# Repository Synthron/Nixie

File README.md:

# Nixie

A Nixie Clock with Z5600M and ESP32

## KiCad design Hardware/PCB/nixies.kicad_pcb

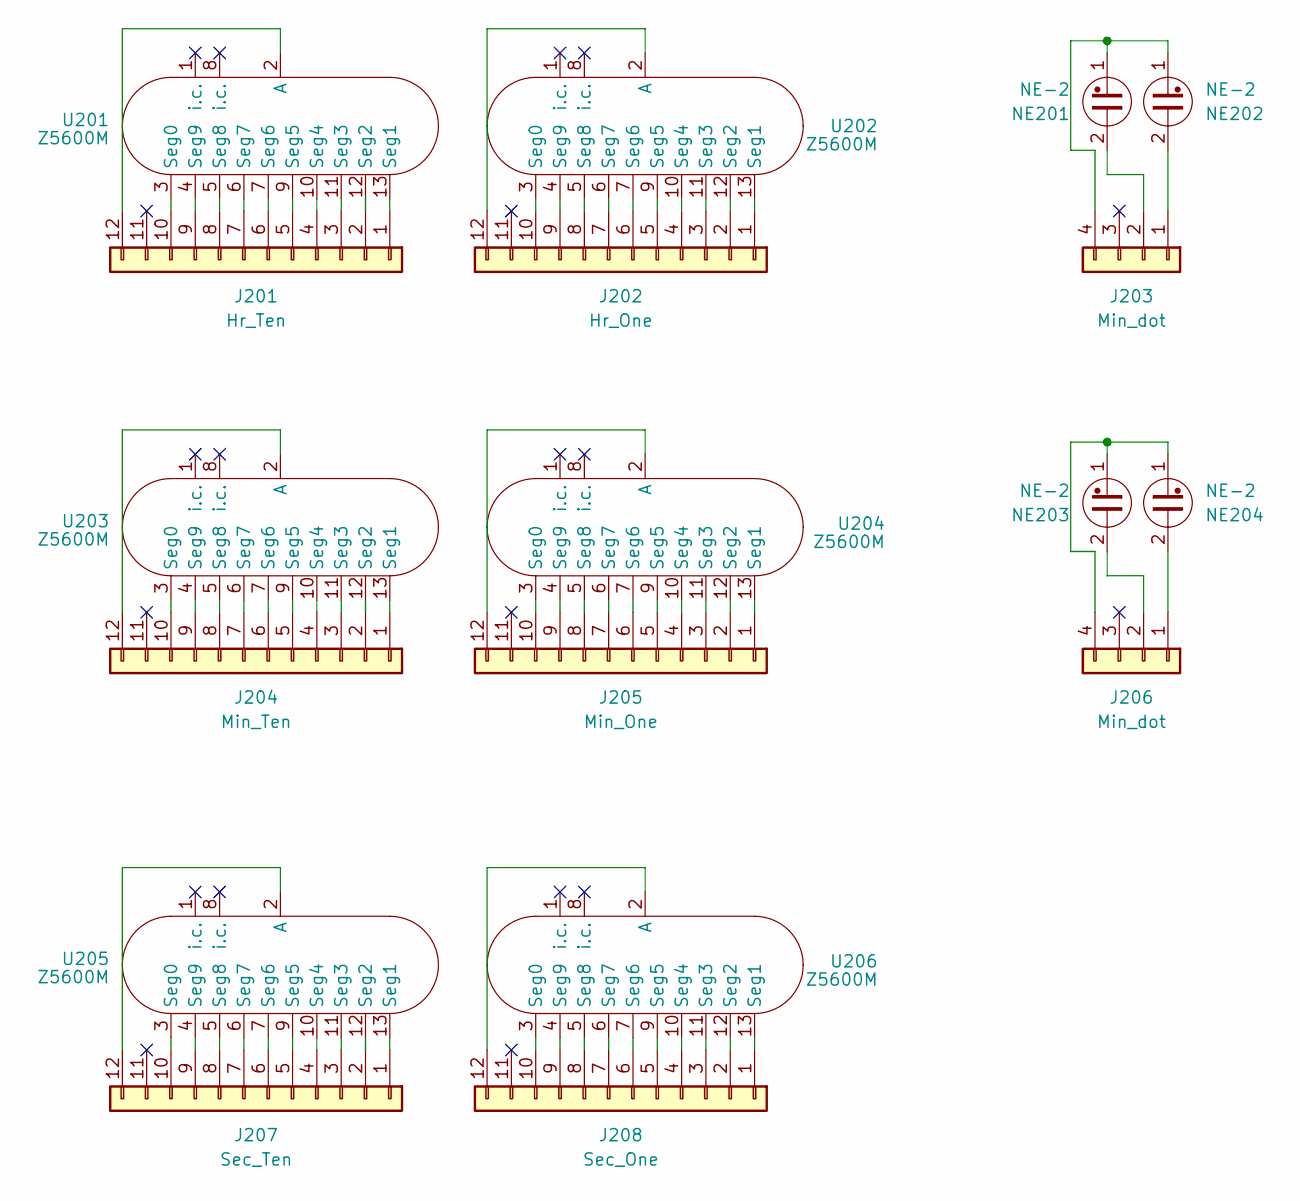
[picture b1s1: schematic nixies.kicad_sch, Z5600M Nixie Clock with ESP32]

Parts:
J201: Hr_Ten; PinSocket_1x12_P2.54mm_Vertical
J202: Hr_One; PinSocket_1x12_P2.54mm_Vertical
J203, J206: Min_dot; PinSocket_1x04_P2.54mm_Vertical
J204: Min_Ten; PinSocket_1x12_P2.54mm_Vertical
J205: Min_One; PinSocket_1x12_P2.54mm_Vertical
J207: Sec_Ten; PinSocket_1x12_P2.54mm_Vertical
J208: Sec_One; PinSocket_1x12_P2.54mm_Vertical
NE201, NE202, NE203, NE204: NE-2; Valve_Glimm
U201, U202, U203, U204, U205, U206: Z5600M; B13B

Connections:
unnamed: J201.1, U201.13 (Seg1)
unnamed: J201.2, U201.12 (Seg2)
unnamed: J201.3, U201.11 (Seg3)
unnamed: J201.4, U201.10 (Seg4)
unnamed: J201.5, U201.9 (Seg5)
unnamed: J201.6, U201.7 (Seg6)
unnamed: J201.7, U201.6 (Seg7)
unnamed: J201.8, U201.5 (Seg8)
unnamed: J201.9, U201.4 (Seg9)
unnamed: J201.10, U201.3 (Seg0)
unnamed: J201.12, U201.2 (A)
unnamed: J202.1, U202.13 (Seg1)
unnamed: J202.2, U202.12 (Seg2)
unnamed: J202.3, U202.11 (Seg3)
unnamed: J202.4, U202.10 (Seg4)
unnamed: J202.5, U202.9 (Seg5)
unnamed: J202.6, U202.7 (Seg6)
unnamed: J202.7, U202.6 (Seg7)
unnamed: J202.8, U202.5 (Seg8)
unnamed: J202.9, U202.4 (Seg9)
unnamed: J202.10, U202.3 (Seg0)
unnamed: J202.12, U202.2 (A)
unnamed: J203.1, NE202.2
unnamed: J203.2, NE201.2
unnamed: J203.4, NE201.1, NE202.1
unnamed: J204.1, U203.13 (Seg1)
unnamed: J204.2, U203.12 (Seg2)
unnamed: J204.3, U203.11 (Seg3)
unnamed: J204.4, U203.10 (Seg4)
unnamed: J204.5, U203.9 (Seg5)
unnamed: J204.6, U203.7 (Seg6)
unnamed: J204.7, U203.6 (Seg7)
unnamed: J204.8, U203.5 (Seg8)
unnamed: J204.9, U203.4 (Seg9)
unnamed: J204.10, U203.3 (Seg0)
unnamed: J204.12, U203.2 (A)
unnamed: J205.1, U204.13 (Seg1)
unnamed: J205.2, U204.12 (Seg2)
unnamed: J205.3, U204.11 (Seg3)
unnamed: J205.4, U204.10 (Seg4)
unnamed: J205.5, U204.9 (Seg5)
unnamed: J205.6, U204.7 (Seg6)
unnamed: J205.7, U204.6 (Seg7)
unnamed: J205.8, U204.5 (Seg8)
unnamed: J205.9, U204.4 (Seg9)
unnamed: J205.10, U204.3 (Seg0)
unnamed: J205.12, U204.2 (A)
unnamed: J206.1, NE204.2
unnamed: J206.2, NE203.2
unnamed: J206.4, NE203.1, NE204.1
unnamed: J207.1, U205.13 (Seg1)
unnamed: J207.2, U205.12 (Seg2)
unnamed: J207.3, U205.11 (Seg3)
unnamed: J207.4, U205.10 (Seg4)
unnamed: J207.5, U205.9 (Seg5)
unnamed: J207.6, U205.7 (Seg6)
unnamed: J207.7, U205.6 (Seg7)
unnamed: J207.8, U205.5 (Seg8)
unnamed: J207.9, U205.4 (Seg9)
unnamed: J207.10, U205.3 (Seg0)
unnamed: J207.12, U205.2 (A)
unnamed: J208.1, U206.13 (Seg1)
unnamed: J208.2, U206.12 (Seg2)
unnamed: J208.3, U206.11 (Seg3)
unnamed: J208.4, U206.10 (Seg4)
unnamed: J208.5, U206.9 (Seg5)
unnamed: J208.6, U206.7 (Seg6)
unnamed: J208.7, U206.6 (Seg7)
unnamed: J208.8, U206.5 (Seg8)
unnamed: J208.9, U206.4 (Seg9)
unnamed: J208.10, U206.3 (Seg0)
unnamed: J208.12, U206.2 (A)

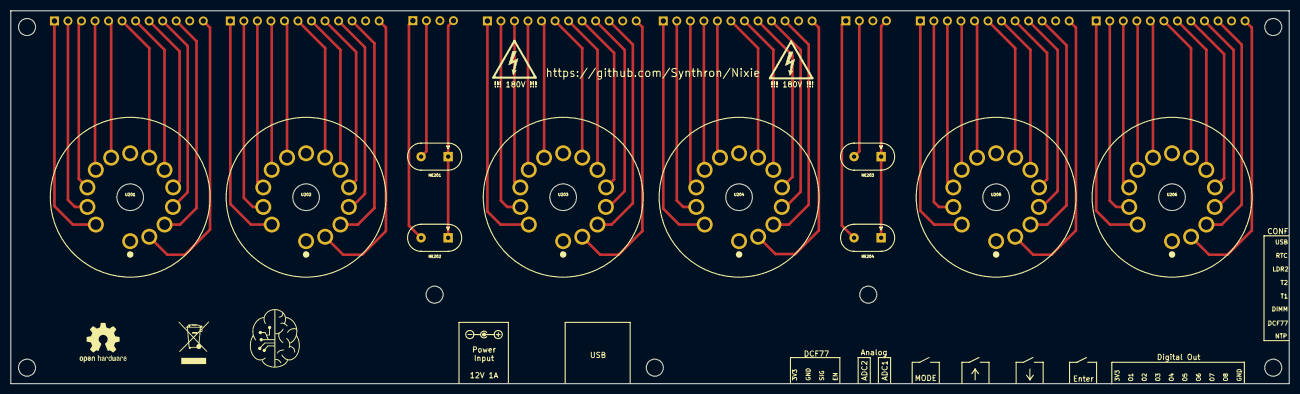
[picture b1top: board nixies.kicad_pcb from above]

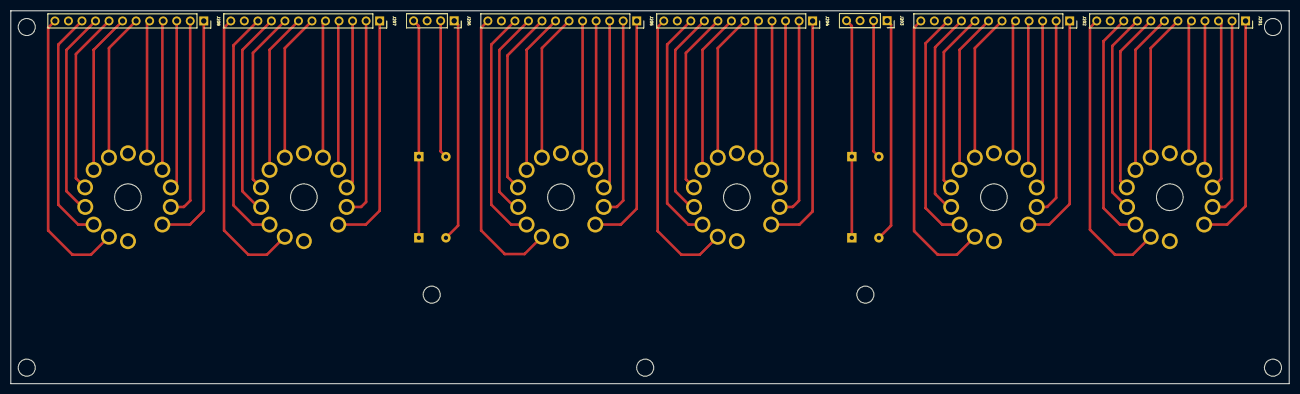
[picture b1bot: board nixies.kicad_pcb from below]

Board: 2 copper layers, 240.0 x 70.0 mm, 18 parts (8 on the bottom side), 72 nets.

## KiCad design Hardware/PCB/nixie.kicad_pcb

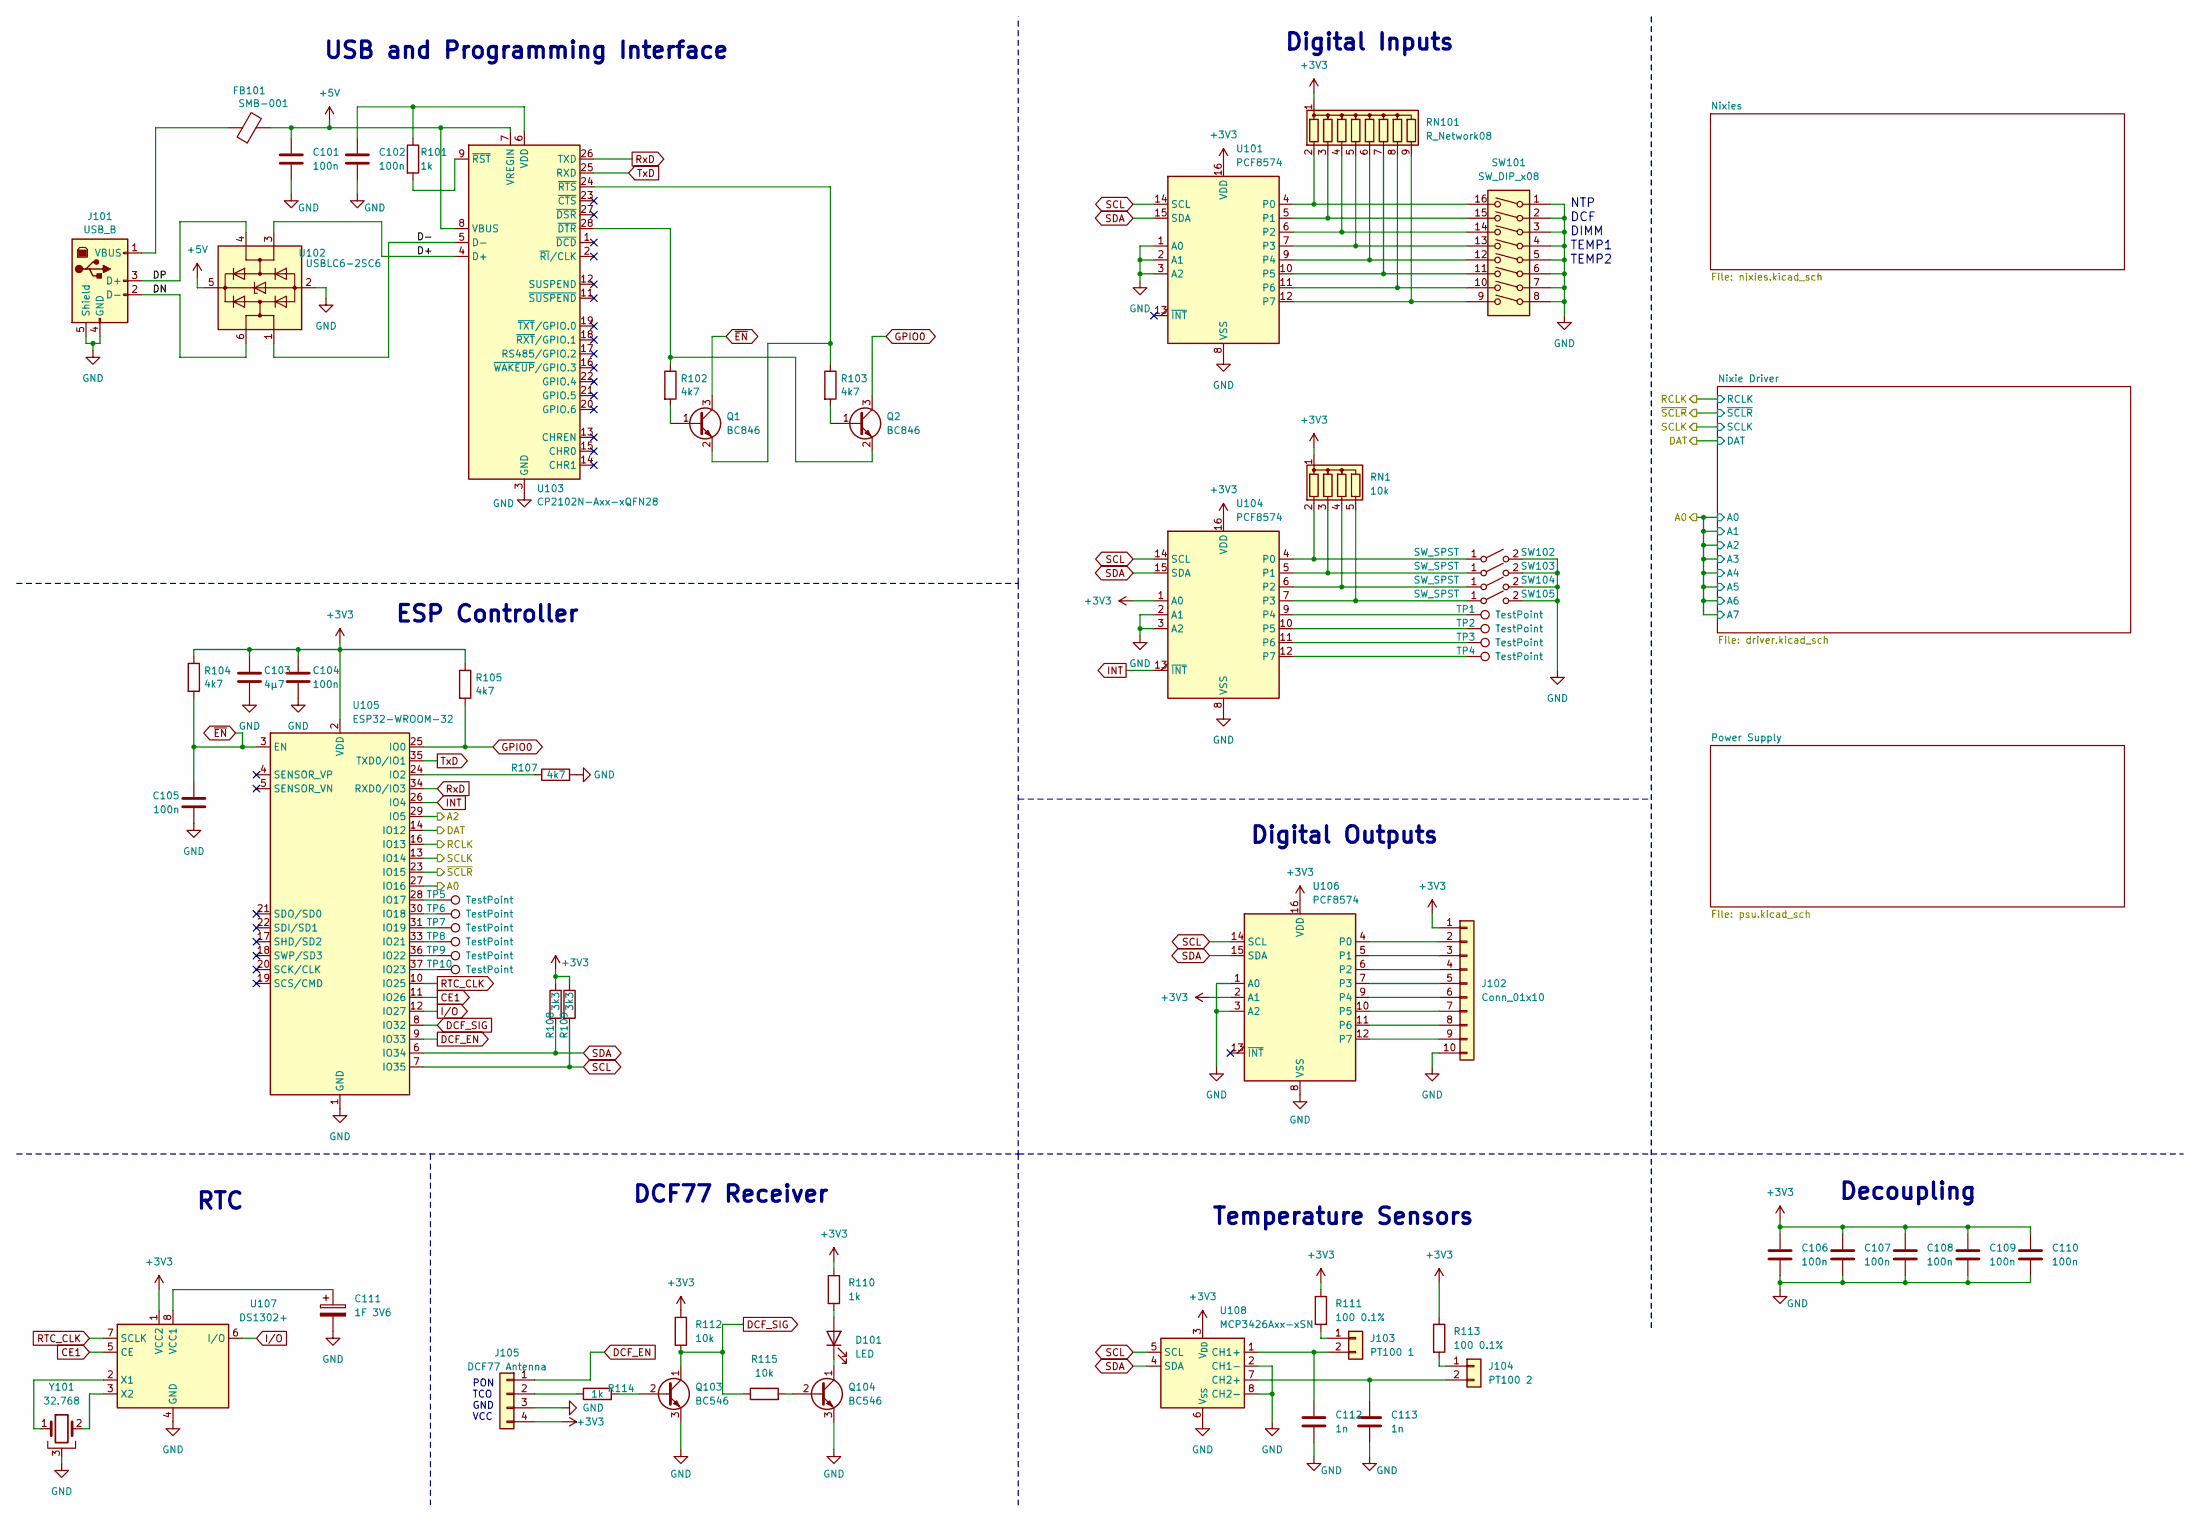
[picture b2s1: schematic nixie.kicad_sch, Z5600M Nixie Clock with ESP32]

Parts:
C101, C102, C104, C105: 100n; C_0805_2012Metric
C103: 4µ7; C_0805_2012Metric
C106, C107, C108, C109, C110: 100n; C_Disc_D3.0mm_W1.6mm_P2.50mm
C111: 1F 3V6; CP_Radial_D21.5mm_P5.00mm
C112, C113: 1n; C_Disc_D3.0mm_W1.6mm_P2.50mm
D101: LED; LED_D3.0mm
FB101: SMB-001; SMB-002
J101: USB_B; USB_B_Lumberg_2411_02_Horizontal
J102: Conn_01x10; PinHeader_1x10_P2.54mm_Vertical
J103: PT100 1; PinHeader_1x02_P2.54mm_Vertical
J104: PT100 2; PinHeader_1x02_P2.54mm_Vertical
J105: DCF77 Antenna; PinHeader_1x04_P2.54mm_Vertical
Q1, Q2: BC846; SOT-23
Q103, Q104: BC546; TO-92
R101: 1k; R_0805_2012Metric
R102, R103, R104, R105, R107: 4k7; R_0805_2012Metric
R108, R109: 3k3; R_0805_2012Metric
R110, R114: 1k; R_Axial_DIN0207_L6.3mm_D2.5mm_P2.54mm_Vertical
R111, R113: 100 0.1%; R_Axial_DIN0207_L6.3mm_D2.5mm_P2.54mm_Vertical
R112, R115: 10k; R_Axial_DIN0207_L6.3mm_D2.5mm_P2.54mm_Vertical
RN1: 10k; R_Array_SIP5
RN101: R_Network08; R_Array_SIP9
SW101: SW_DIP_x08; SW_DIP_SPSTx08_Piano_CTS_Series194-8MSTN_W7.62mm_P2.54mm
SW102, SW103, SW104, SW105: SW_SPST; SW_SPST_Omron_B3F-315x_Angled
TP1, TP2, TP3, TP4, TP5, TP6, TP7, TP8, TP9, TP10: TestPoint; Pin_D1.0mm_L10.0mm
U101, U104, U106: PCF8574; DIP-16_W7.62mm
U102: USBLC6-2SC6; SOT-23-6
U103: CP2102N-Axx-xQFN28; QFN-28-1EP_5x5mm_P0.5mm_EP3.35x3.35mm_ThermalVias
U105: ESP32-WROOM-32
U107: DS1302+; DIP-8_W7.62mm
U108: MCP3426Axx-xSN; SOIC-8_3.9x4.9mm_P1.27mm
Y101: 32.768; Crystal_SMD_MicroCrystal_MS1V-T1K

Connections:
+3V3: C103.1, C104.1, C106.1, C107.1, C108.1, C109.1, C110.1, J102.1, J105.4, R104.1, R105.1, R108.1, R109.1, R110.1, R111.1, R112.1, R113.1, RN1.1 (common), RN101.1 (common), U101.16 (VDD), U104.1 (A0), U104.16 (VDD), U105.2 (VDD), U106.2 (A1), U106.16 (VDD), U107.1 (VCC2), U108.3 (V_{DD}); also elsewhere on the board
+5V: C101.1, FB101.2, U102.5 (VBUS), U103.7 (VREGIN), U103.8 (VBUS); also elsewhere on the board
/A0: U105.27 (IO16); also elsewhere on the board
/A2: U105.29 (IO5)
/D+: U102.3 (I/O2), U103.4 (D+)
/D-: U102.1 (I/O1), U103.5 (D-)
/DAT: U105.14 (IO12); also elsewhere on the board
/DN: J101.2 (D-), U102.6 (I/O1)
/DP: J101.3 (D+), U102.4 (I/O2)
/RCLK: U105.16 (IO13); also elsewhere on the board
/SCLK: U105.13 (IO14); also elsewhere on the board
/~SCLR: U105.23 (IO15); also elsewhere on the board
CE1: U105.11 (IO26), U107.5 (CE)
DCF_EN: J105.1, U105.9 (IO33)
DCF_SIG: Q103.1 (C), R112.2, R115.1, U105.8 (IO32)
GND: C101.2, C102.2, C103.2, C104.2, C105.2, C106.2, C107.2, C108.2, C109.2, C110.2, C111.2, C112.2, C113.2, J101.4 (GND), J101.5 (Shield), J102.10, J105.3, Q103.3 (E), Q104.3 (E), R107.2, SW101.1, SW101.2, SW101.3, SW101.4, SW101.5, SW101.6, SW101.7, SW101.8, SW102.2 (B), SW103.2 (B), SW104.2 (B), SW105.2 (B), U101.1 (A0), U101.2 (A1), U101.3 (A2), U101.8 (VSS), U102.2 (GND), U103.3 (GND), U103.29 (GND), U104.2 (A1), U104.3 (A2), U104.8 (VSS), U105.1 (GND), U105.15 (GND), U105.38 (GND), U105.39 (GND), U106.1 (A0), U106.3 (A2), U106.8 (VSS), U107.4 (GND), U108.2 (CH1-), U108.6 (V_{SS}), U108.8 (CH2-), Y101.3; also elsewhere on the board
GPIO0: Q2.3 (C), R105.2, U105.25 (IO0)
INT: U104.13 (~INT), U105.26 (IO4)
I/O: U105.12 (IO27), U107.6 (I/O)
unnamed: D101.2 (A), R110.2
unnamed: D101.1 (K), Q104.1 (C)
unnamed: FB101.1, J101.1 (VBUS)
unnamed: J102.2, U106.4 (P0)
unnamed: J102.3, U106.5 (P1)
unnamed: J102.4, U106.6 (P2)
unnamed: J102.5, U106.7 (P3)
unnamed: J102.6, U106.9 (P4)
unnamed: J102.7, U106.10 (P5)
unnamed: J102.8, U106.11 (P6)
unnamed: J102.9, U106.12 (P7)
unnamed: J103.1, R111.2
unnamed: C112.1, J103.2, U108.1 (CH1+)
unnamed: J104.1, R113.2
unnamed: C113.1, J104.2, U108.7 (CH2+)
unnamed: J105.2, R114.1
unnamed: Q1.1 (B), R102.2
unnamed: Q1.2 (E), R103.1, U103.24 (~RTS)
unnamed: Q2.1 (B), R103.2
unnamed: Q2.2 (E), R102.1, U103.28 (~DTR)
unnamed: Q103.2 (B), R114.2
unnamed: Q104.2 (B), R115.2
unnamed: RN1.2 (R1), SW102.1 (A), U104.4 (P0)
unnamed: RN1.3 (R2), SW103.1 (A), U104.5 (P1)
unnamed: RN1.4 (R3), SW104.1 (A), U104.6 (P2)
unnamed: RN1.5 (R4), SW105.1 (A), U104.7 (P3)
unnamed: RN101.2 (R1), SW101.16, U101.4 (P0)
unnamed: RN101.3 (R2), SW101.15, U101.5 (P1)
unnamed: RN101.4 (R3), SW101.14, U101.6 (P2)
unnamed: RN101.5 (R4), SW101.13, U101.7 (P3)
unnamed: RN101.6 (R5), SW101.12, U101.9 (P4)
unnamed: RN101.7 (R6), SW101.11, U101.10 (P5)
unnamed: RN101.8 (R7), SW101.10, U101.11 (P6)
unnamed: RN101.9 (R8), SW101.9, U101.12 (P7)
unnamed: C102.1, R101.1, U103.6 (VDD)
unnamed: R101.2, U103.9 (~RST)
unnamed: TP1.1, U104.9 (P4)
unnamed: TP2.1, U104.10 (P5)
unnamed: TP3.1, U104.11 (P6)
unnamed: TP4.1, U104.12 (P7)
unnamed: R107.1, U105.24 (IO2)
unnamed: TP5.1, U105.28 (IO17)
unnamed: TP6.1, U105.30 (IO18)
unnamed: TP7.1, U105.31 (IO19)
unnamed: TP8.1, U105.33 (IO21)
unnamed: TP9.1, U105.36 (IO22)
unnamed: TP10.1, U105.37 (IO23)
unnamed: C111.1, U107.8 (VCC1)
unnamed: U107.2 (X1), Y101.1
unnamed: U107.3 (X2), Y101.2
RTC_CLK: U105.10 (IO25), U107.7 (SCLK)
RxD: U103.26 (TXD), U105.34 (RXD0/IO3)
SCL: R109.2, U101.14 (SCL), U104.14 (SCL), U105.7 (IO35), U106.14 (SCL), U108.5 (SCL)
SDA: R108.2, U101.15 (SDA), U104.15 (SDA), U105.6 (IO34), U106.15 (SDA), U108.4 (SDA)
TxD: U103.25 (RXD), U105.35 (TXD0/IO1)
~EN: C105.1, Q1.3 (C), R104.2, U105.3 (EN)

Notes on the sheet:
NTP DCF DIMM TEMP1 TEMP2
USB and Programming Interface
Temperature Sensors
PON TCO GND VCC
DCF77 Receiver
Decoupling
ESP Controller
Digital Outputs
RTC
Digital Inputs

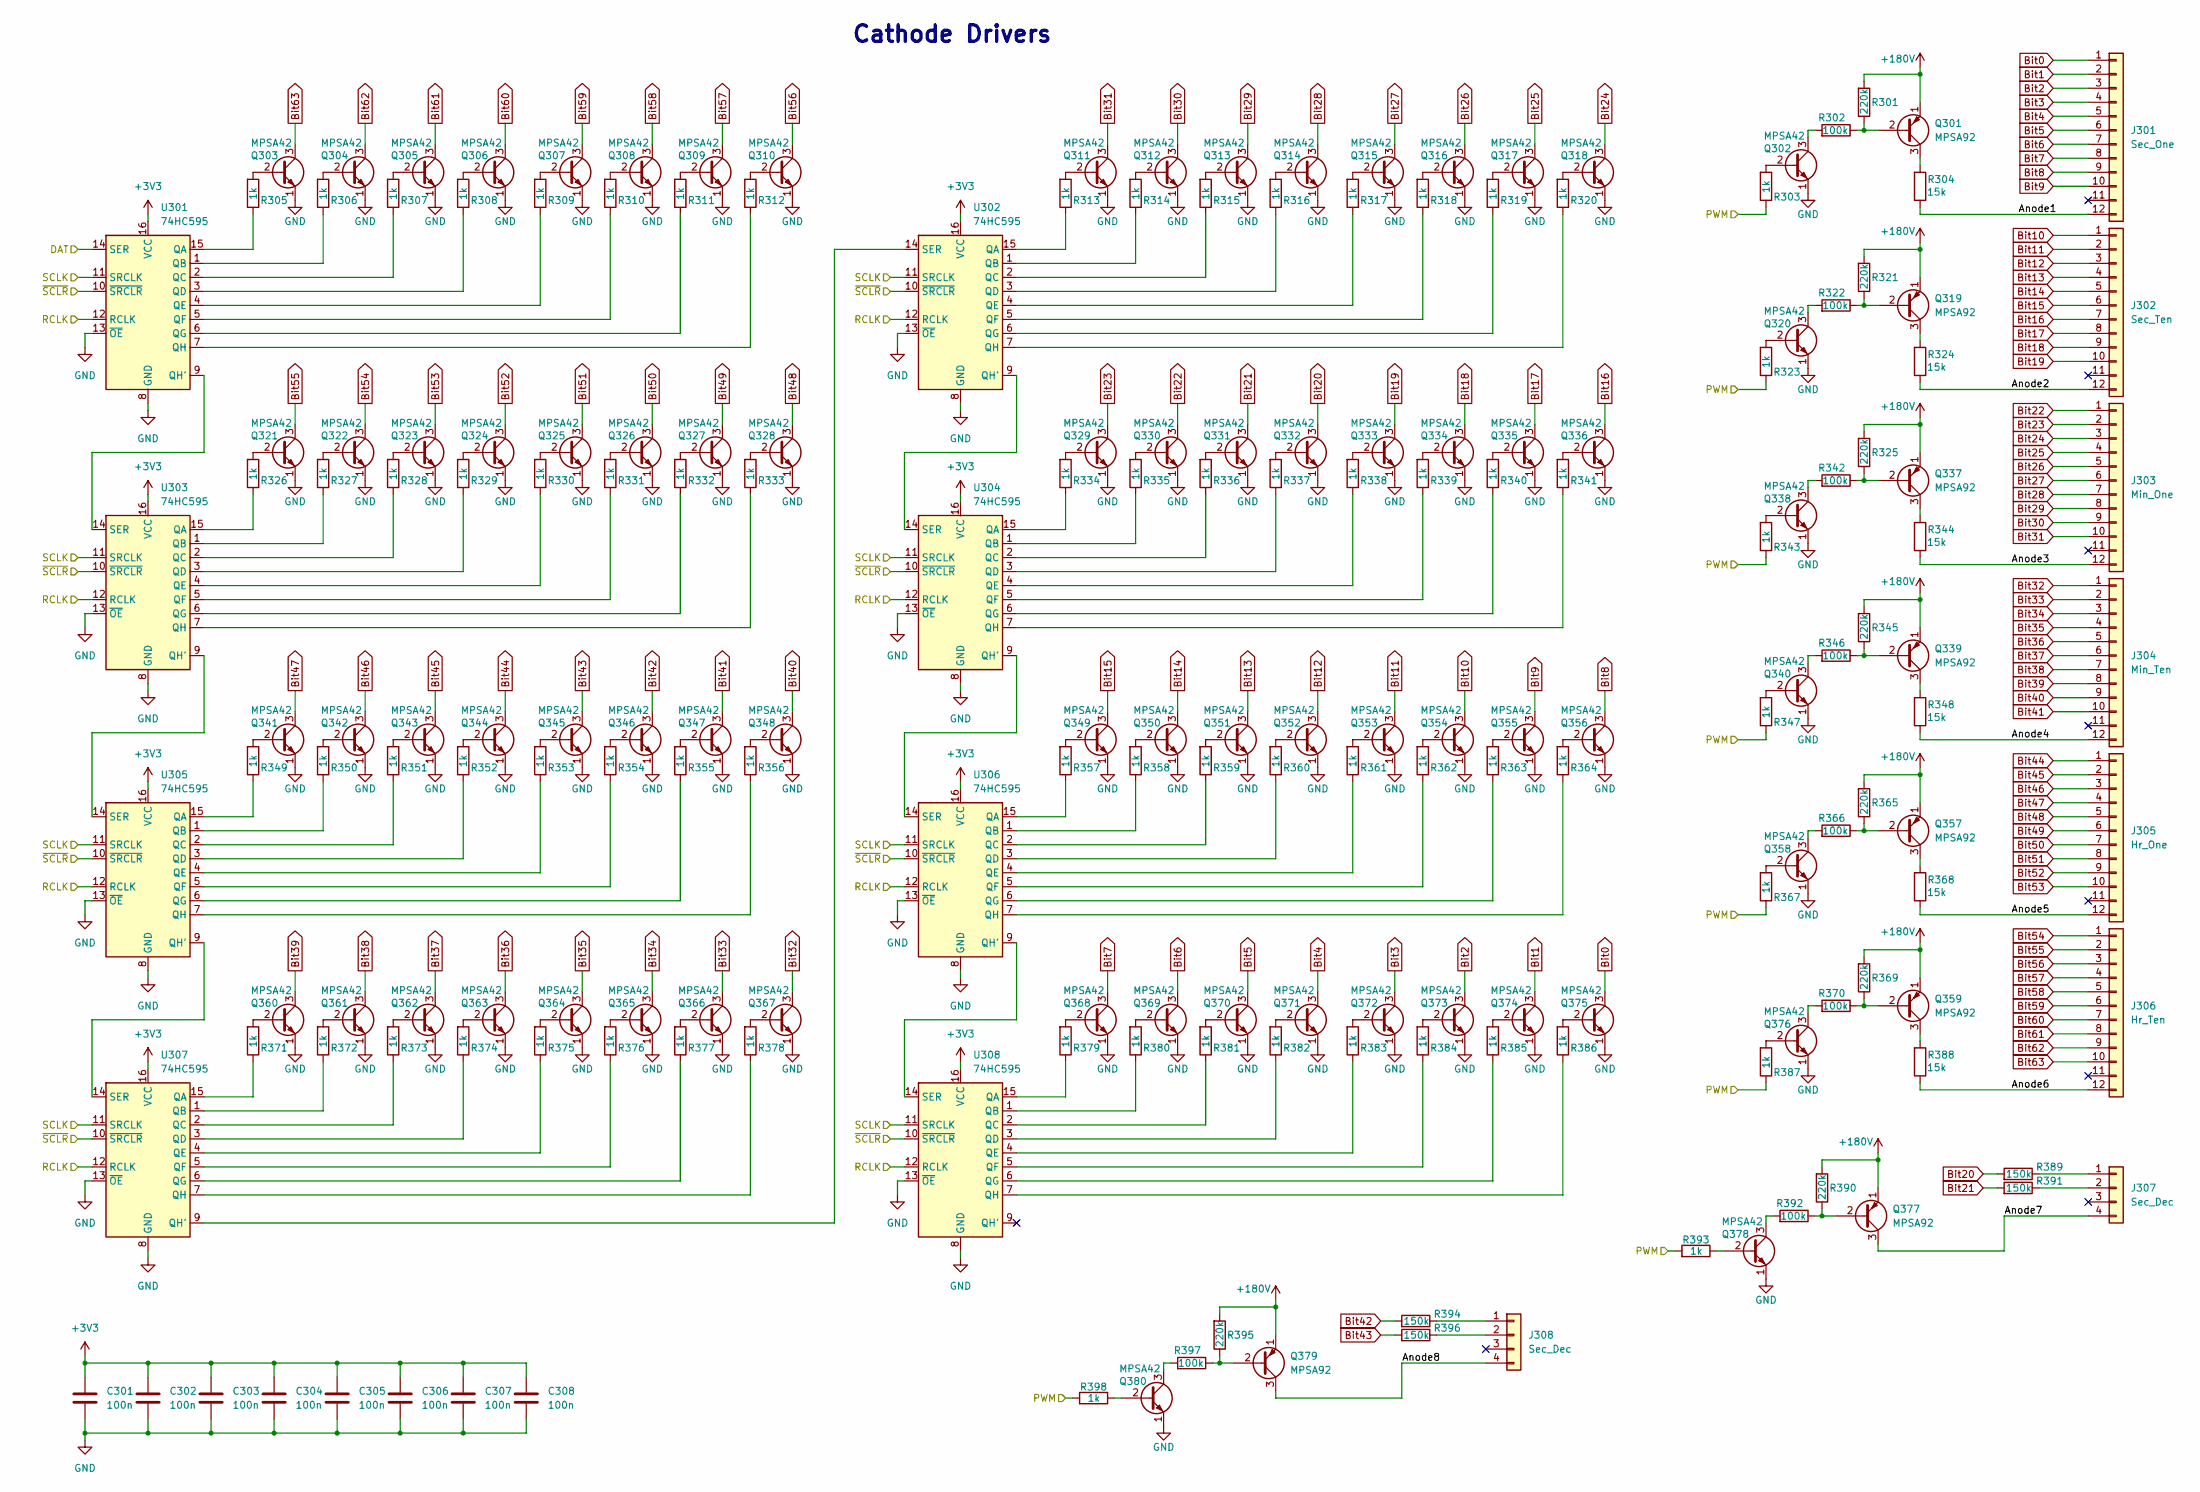
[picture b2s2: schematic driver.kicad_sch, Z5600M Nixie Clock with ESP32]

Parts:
C301, C302, C303, C304, C305, C306, C307, C308: 100n; C_Disc_D3.0mm_W1.6mm_P2.50mm
J301: Sec_One; PinHeader_1x12_P2.54mm_Vertical
J302: Sec_Ten; PinHeader_1x12_P2.54mm_Vertical
J303: Min_One; PinHeader_1x12_P2.54mm_Vertical
J304: Min_Ten; PinHeader_1x12_P2.54mm_Vertical
J305: Hr_One; PinHeader_1x12_P2.54mm_Vertical
J306: Hr_Ten; PinHeader_1x12_P2.54mm_Vertical
J307, J308: Sec_Dec; PinHeader_1x04_P2.54mm_Vertical
Q301, Q319, Q337, Q339, Q357, Q359, Q377, Q379: MPSA92; TO-92
Q302, Q303, Q304, Q305, Q306, Q307, Q308, Q309, Q310, Q311, Q312, Q313, Q314, Q315, Q316, Q317, Q318, Q320, Q321, Q322, Q323, Q324, Q325, Q326, Q327, Q328, Q329, Q330, Q331, Q332, Q333, Q334, Q335, Q336, Q338, Q340, Q341, Q342, Q343, Q344, Q345, Q346, Q347, Q348, Q349, Q350, Q351, Q352, Q353, Q354, Q355, Q356, Q358, Q360, Q361, Q362, Q363, Q364, Q365, Q366, Q367, Q368, Q369, Q370, Q371, Q372, Q373, Q374, Q375, Q376, Q378, Q380: MPSA42; TO-92
R301, R321, R325, R345, R365, R369, R390, R395: 220k; R_Axial_DIN0207_L6.3mm_D2.5mm_P2.54mm_Vertical
R302, R322, R342, R346, R366, R370, R392, R397: 100k; R_Axial_DIN0207_L6.3mm_D2.5mm_P2.54mm_Vertical
R303, R343, R367, R393: 1k; R_Axial_DIN0207_L6.3mm_D2.5mm_P7.62mm_Horizontal
R304, R324, R344, R348, R368, R388: 15k; R_Axial_DIN0207_L6.3mm_D2.5mm_P2.54mm_Vertical
R305, R306, R307, R308, R309, R310, R311, R312, R313, R314, R315, R316, R317, R318, R319, R320, R323, R326, R327, R328, R329, R330, R331, R332, R333, R334, R335, R336, R337, R338, R339, R340, R341, R347, R349, R350, R351, R352, R353, R354, R355, R356, R357, R358, R359, R360, R361, R362, R363, R364, R371, R372, R373, R374, R375, R376, R377, R378, R379, R380, R381, R382, R383, R384, R385, R386, R387, R398: 1k; R_Axial_DIN0207_L6.3mm_D2.5mm_P2.54mm_Vertical
R389, R391, R394, R396: 150k; R_Axial_DIN0207_L6.3mm_D2.5mm_P2.54mm_Vertical
U301, U302, U303, U304, U305, U306, U307, U308: 74HC595; DIP-16_W7.62mm

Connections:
+3V3: C301.1, C302.1, C303.1, C304.1, C305.1, C306.1, C307.1, C308.1, U301.16 (VCC), U302.16 (VCC), U303.16 (VCC), U304.16 (VCC), U305.16 (VCC), U306.16 (VCC), U307.16 (VCC), U308.16 (VCC); also elsewhere on the board
+180V: Q301.1 (E), Q319.1 (E), Q337.1 (E), Q339.1 (E), Q357.1 (E), Q359.1 (E), Q377.1 (E), Q379.1 (E), R301.2, R321.2, R325.2, R345.2, R365.2, R369.2, R390.2, R395.2; also elsewhere on the board
/A0: R303.1, R323.1, R343.1, R347.1, R367.1, R387.1, R393.2, R398.2; also elsewhere on the board
/DAT: U301.14 (SER); also elsewhere on the board
/Nixie Driver/Anode1: J301.12, R304.1
/Nixie Driver/Anode2: J302.12, R324.1
/Nixie Driver/Anode3: J303.12, R344.1
/Nixie Driver/Anode4: J304.12, R348.1
/Nixie Driver/Anode5: J305.12, R368.1
/Nixie Driver/Anode6: J306.12, R388.1
/Nixie Driver/Anode7: J307.4, Q377.3 (C)
/Nixie Driver/Anode8: J308.4, Q379.3 (C)
/RCLK: U301.12 (RCLK), U302.12 (RCLK), U303.12 (RCLK), U304.12 (RCLK), U305.12 (RCLK), U306.12 (RCLK), U307.12 (RCLK), U308.12 (RCLK); also elsewhere on the board
/SCLK: U301.11 (SRCLK), U302.11 (SRCLK), U303.11 (SRCLK), U304.11 (SRCLK), U305.11 (SRCLK), U306.11 (SRCLK), U307.11 (SRCLK), U308.11 (SRCLK); also elsewhere on the board
/~SCLR: U301.10 (~SRCLR), U302.10 (~SRCLR), U303.10 (~SRCLR), U304.10 (~SRCLR), U305.10 (~SRCLR), U306.10 (~SRCLR), U307.10 (~SRCLR), U308.10 (~SRCLR); also elsewhere on the board
Bit0: J301.1, Q375.3 (C)
Bit1: J301.2, Q374.3 (C)
Bit2: J301.3, Q373.3 (C)
Bit3: J301.4, Q372.3 (C)
Bit4: J301.5, Q371.3 (C)
Bit5: J301.6, Q370.3 (C)
Bit6: J301.7, Q369.3 (C)
Bit7: J301.8, Q368.3 (C)
Bit8: J301.9, Q356.3 (C)
Bit9: J301.10, Q355.3 (C)
Bit10: J302.1, Q354.3 (C)
Bit11: J302.2, Q353.3 (C)
Bit12: J302.3, Q352.3 (C)
Bit13: J302.4, Q351.3 (C)
Bit14: J302.5, Q350.3 (C)
Bit15: J302.6, Q349.3 (C)
Bit16: J302.7, Q336.3 (C)
Bit17: J302.8, Q335.3 (C)
Bit18: J302.9, Q334.3 (C)
Bit19: J302.10, Q333.3 (C)
Bit20: Q332.3 (C), R389.2
Bit21: Q331.3 (C), R391.2
Bit22: J303.1, Q330.3 (C)
Bit23: J303.2, Q329.3 (C)
Bit24: J303.3, Q318.3 (C)
Bit25: J303.4, Q317.3 (C)
Bit26: J303.5, Q316.3 (C)
Bit27: J303.6, Q315.3 (C)
Bit28: J303.7, Q314.3 (C)
Bit29: J303.8, Q313.3 (C)
Bit30: J303.9, Q312.3 (C)
Bit31: J303.10, Q311.3 (C)
Bit32: J304.1, Q367.3 (C)
Bit33: J304.2, Q366.3 (C)
Bit34: J304.3, Q365.3 (C)
Bit35: J304.4, Q364.3 (C)
Bit36: J304.5, Q363.3 (C)
Bit37: J304.6, Q362.3 (C)
Bit38: J304.7, Q361.3 (C)
Bit39: J304.8, Q360.3 (C)
Bit40: J304.9, Q348.3 (C)
Bit41: J304.10, Q347.3 (C)
Bit42: Q346.3 (C), R394.2
Bit43: Q345.3 (C), R396.2
Bit44: J305.1, Q344.3 (C)
Bit45: J305.2, Q343.3 (C)
Bit46: J305.3, Q342.3 (C)
Bit47: J305.4, Q341.3 (C)
Bit48: J305.5, Q328.3 (C)
Bit49: J305.6, Q327.3 (C)
Bit50: J305.7, Q326.3 (C)
Bit51: J305.8, Q325.3 (C)
Bit52: J305.9, Q324.3 (C)
Bit53: J305.10, Q323.3 (C)
Bit54: J306.1, Q322.3 (C)
Bit55: J306.2, Q321.3 (C)
Bit56: J306.3, Q310.3 (C)
Bit57: J306.4, Q309.3 (C)
Bit58: J306.5, Q308.3 (C)
Bit59: J306.6, Q307.3 (C)
Bit60: J306.7, Q306.3 (C)
Bit61: J306.8, Q305.3 (C)
Bit62: J306.9, Q304.3 (C)
Bit63: J306.10, Q303.3 (C)
GND: C301.2, C302.2, C303.2, C304.2, C305.2, C306.2, C307.2, C308.2, Q302.1 (E), Q303.1 (E), Q304.1 (E), Q305.1 (E), Q306.1 (E), Q307.1 (E), Q308.1 (E), Q309.1 (E), Q310.1 (E), Q311.1 (E), Q312.1 (E), Q313.1 (E), Q314.1 (E), Q315.1 (E), Q316.1 (E), Q317.1 (E), Q318.1 (E), Q320.1 (E), Q321.1 (E), Q322.1 (E), Q323.1 (E), Q324.1 (E), Q325.1 (E), Q326.1 (E), Q327.1 (E), Q328.1 (E), Q329.1 (E), Q330.1 (E), Q331.1 (E), Q332.1 (E), Q333.1 (E), Q334.1 (E), Q335.1 (E), Q336.1 (E), Q338.1 (E), Q340.1 (E), Q341.1 (E), Q342.1 (E), Q343.1 (E), Q344.1 (E), Q345.1 (E), Q346.1 (E), Q347.1 (E), Q348.1 (E), Q349.1 (E), Q350.1 (E), Q351.1 (E), Q352.1 (E), Q353.1 (E), Q354.1 (E), Q355.1 (E), Q356.1 (E), Q358.1 (E), Q360.1 (E), Q361.1 (E), Q362.1 (E), Q363.1 (E), Q364.1 (E), Q365.1 (E), Q366.1 (E), Q367.1 (E), Q368.1 (E), Q369.1 (E), Q370.1 (E), Q371.1 (E), Q372.1 (E), Q373.1 (E), Q374.1 (E), Q375.1 (E), Q376.1 (E), Q378.1 (E), Q380.1 (E), U301.8 (GND), U301.13 (~OE), U302.8 (GND), U302.13 (~OE), U303.8 (GND), U303.13 (~OE), U304.8 (GND), U304.13 (~OE), U305.8 (GND), U305.13 (~OE), U306.8 (GND), U306.13 (~OE), U307.8 (GND), U307.13 (~OE), U308.8 (GND), U308.13 (~OE); also elsewhere on the board
unnamed: J307.1, R389.1
unnamed: J307.2, R391.1
unnamed: J308.1, R394.1
unnamed: J308.2, R396.1
unnamed: Q301.2 (B), R301.1, R302.1
unnamed: Q301.3 (C), R304.2
unnamed: Q302.2 (B), R303.2
unnamed: Q302.3 (C), R302.2
unnamed: Q303.2 (B), R305.2
unnamed: Q304.2 (B), R306.2
unnamed: Q305.2 (B), R307.2
unnamed: Q306.2 (B), R308.2
unnamed: Q307.2 (B), R309.2
unnamed: Q308.2 (B), R310.2
unnamed: Q309.2 (B), R311.2
unnamed: Q310.2 (B), R312.2
unnamed: Q311.2 (B), R313.2
unnamed: Q312.2 (B), R314.2
unnamed: Q313.2 (B), R315.2
unnamed: Q314.2 (B), R316.2
unnamed: Q315.2 (B), R317.2
unnamed: Q316.2 (B), R318.2
unnamed: Q317.2 (B), R319.2
unnamed: Q318.2 (B), R320.2
unnamed: Q319.2 (B), R321.1, R322.1
unnamed: Q319.3 (C), R324.2
unnamed: Q320.2 (B), R323.2
unnamed: Q320.3 (C), R322.2
unnamed: Q321.2 (B), R326.2
unnamed: Q322.2 (B), R327.2
unnamed: Q323.2 (B), R328.2
unnamed: Q324.2 (B), R329.2
unnamed: Q325.2 (B), R330.2
unnamed: Q326.2 (B), R331.2
unnamed: Q327.2 (B), R332.2
unnamed: Q328.2 (B), R333.2
unnamed: Q329.2 (B), R334.2
unnamed: Q330.2 (B), R335.2
unnamed: Q331.2 (B), R336.2
unnamed: Q332.2 (B), R337.2
unnamed: Q333.2 (B), R338.2
unnamed: Q334.2 (B), R339.2
unnamed: Q335.2 (B), R340.2
unnamed: Q336.2 (B), R341.2
unnamed: Q337.2 (B), R325.1, R342.1
unnamed: Q337.3 (C), R344.2
unnamed: Q338.2 (B), R343.2
unnamed: Q338.3 (C), R342.2
unnamed: Q339.2 (B), R345.1, R346.1
unnamed: Q339.3 (C), R348.2
unnamed: Q340.2 (B), R347.2
unnamed: Q340.3 (C), R346.2
unnamed: Q341.2 (B), R349.2
unnamed: Q342.2 (B), R350.2
unnamed: Q343.2 (B), R351.2
unnamed: Q344.2 (B), R352.2
unnamed: Q345.2 (B), R353.2
unnamed: Q346.2 (B), R354.2
unnamed: Q347.2 (B), R355.2
unnamed: Q348.2 (B), R356.2
unnamed: Q349.2 (B), R357.2
unnamed: Q350.2 (B), R358.2
unnamed: Q351.2 (B), R359.2
unnamed: Q352.2 (B), R360.2
unnamed: Q353.2 (B), R361.2
unnamed: Q354.2 (B), R362.2
unnamed: Q355.2 (B), R363.2
unnamed: Q356.2 (B), R364.2
unnamed: Q357.2 (B), R365.1, R366.1
unnamed: Q357.3 (C), R368.2
unnamed: Q358.2 (B), R367.2
unnamed: Q358.3 (C), R366.2
unnamed: Q359.2 (B), R369.1, R370.1
unnamed: Q359.3 (C), R388.2
unnamed: Q360.2 (B), R371.2
unnamed: Q361.2 (B), R372.2
unnamed: Q362.2 (B), R373.2
unnamed: Q363.2 (B), R374.2
unnamed: Q364.2 (B), R375.2
unnamed: Q365.2 (B), R376.2
unnamed: Q366.2 (B), R377.2
unnamed: Q367.2 (B), R378.2
unnamed: Q368.2 (B), R379.2
unnamed: Q369.2 (B), R380.2
unnamed: Q370.2 (B), R381.2
unnamed: Q371.2 (B), R382.2
unnamed: Q372.2 (B), R383.2
unnamed: Q373.2 (B), R384.2
unnamed: Q374.2 (B), R385.2
unnamed: Q375.2 (B), R386.2
unnamed: Q376.2 (B), R387.2
unnamed: Q376.3 (C), R370.2
unnamed: Q377.2 (B), R390.1, R392.1
unnamed: Q378.2 (B), R393.1
unnamed: Q378.3 (C), R392.2
unnamed: Q379.2 (B), R395.1, R397.1
unnamed: Q380.2 (B), R398.1
unnamed: Q380.3 (C), R397.2
unnamed: R305.1, U301.15 (QA)
unnamed: R306.1, U301.1 (QB)
unnamed: R307.1, U301.2 (QC)
unnamed: R308.1, U301.3 (QD)
unnamed: R309.1, U301.4 (QE)
unnamed: R310.1, U301.5 (QF)
unnamed: R311.1, U301.6 (QG)
unnamed: U301.9 (QH'), U303.14 (SER)
unnamed: R312.1, U301.7 (QH)
unnamed: R313.1, U302.15 (QA)
unnamed: R314.1, U302.1 (QB)
unnamed: R315.1, U302.2 (QC)
unnamed: R316.1, U302.3 (QD)
unnamed: R317.1, U302.4 (QE)
unnamed: R318.1, U302.5 (QF)
unnamed: R319.1, U302.6 (QG)
unnamed: U302.9 (QH'), U304.14 (SER)
unnamed: R320.1, U302.7 (QH)
unnamed: U302.14 (SER), U307.9 (QH')
unnamed: R326.1, U303.15 (QA)
unnamed: R327.1, U303.1 (QB)
unnamed: R328.1, U303.2 (QC)
unnamed: R329.1, U303.3 (QD)
unnamed: R330.1, U303.4 (QE)
unnamed: R331.1, U303.5 (QF)
unnamed: R332.1, U303.6 (QG)
unnamed: U303.9 (QH'), U305.14 (SER)
unnamed: R333.1, U303.7 (QH)
unnamed: R334.1, U304.15 (QA)
unnamed: R335.1, U304.1 (QB)
unnamed: R336.1, U304.2 (QC)
unnamed: R337.1, U304.3 (QD)
unnamed: R338.1, U304.4 (QE)
unnamed: R339.1, U304.5 (QF)
unnamed: R340.1, U304.6 (QG)
unnamed: U304.9 (QH'), U306.14 (SER)
unnamed: R341.1, U304.7 (QH)
unnamed: R349.1, U305.15 (QA)
unnamed: R350.1, U305.1 (QB)
unnamed: R351.1, U305.2 (QC)
unnamed: R352.1, U305.3 (QD)
unnamed: R353.1, U305.4 (QE)
unnamed: R354.1, U305.5 (QF)
unnamed: R355.1, U305.6 (QG)
unnamed: U305.9 (QH'), U307.14 (SER)
unnamed: R356.1, U305.7 (QH)
unnamed: R357.1, U306.15 (QA)
unnamed: R358.1, U306.1 (QB)
unnamed: R359.1, U306.2 (QC)
unnamed: R360.1, U306.3 (QD)
unnamed: R361.1, U306.4 (QE)
unnamed: R362.1, U306.5 (QF)
unnamed: R363.1, U306.6 (QG)
unnamed: U306.9 (QH'), U308.14 (SER)
unnamed: R364.1, U306.7 (QH)
unnamed: R371.1, U307.15 (QA)
unnamed: R372.1, U307.1 (QB)
unnamed: R373.1, U307.2 (QC)
unnamed: R374.1, U307.3 (QD)
unnamed: R375.1, U307.4 (QE)
unnamed: R376.1, U307.5 (QF)
unnamed: R377.1, U307.6 (QG)
unnamed: R378.1, U307.7 (QH)
unnamed: R379.1, U308.15 (QA)
unnamed: R380.1, U308.1 (QB)
unnamed: R381.1, U308.2 (QC)
unnamed: R382.1, U308.3 (QD)
unnamed: R383.1, U308.4 (QE)
unnamed: R384.1, U308.5 (QF)
unnamed: R385.1, U308.6 (QG)
unnamed: R386.1, U308.7 (QH)

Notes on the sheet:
Cathode Drivers
